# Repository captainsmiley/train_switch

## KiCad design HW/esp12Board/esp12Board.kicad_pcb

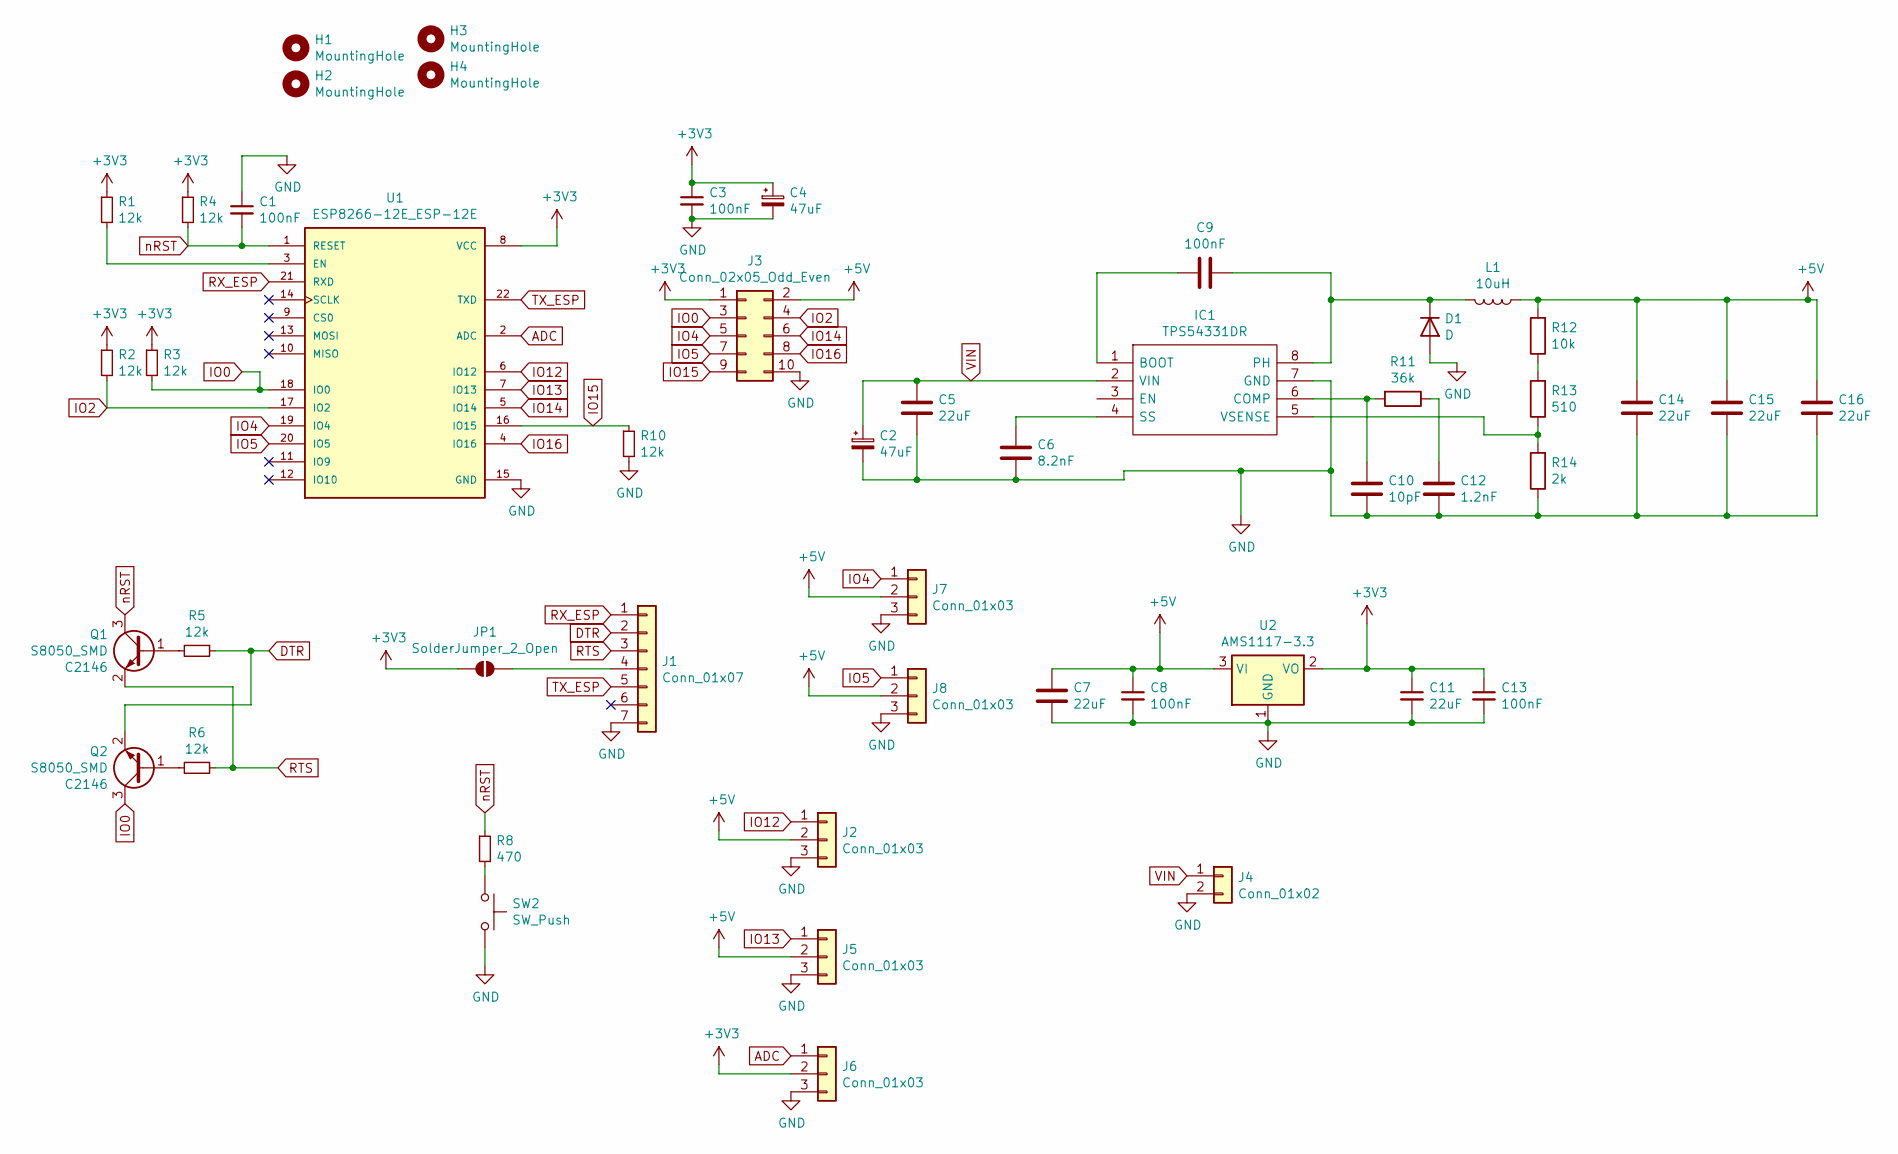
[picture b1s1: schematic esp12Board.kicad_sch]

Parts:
C1, C3, C8, C9, C13: 100nF; C_0805_2012Metric_Pad1.15x1.40mm_HandSolder; LCSC C49678
C2, C4: 47uF; CP_Elec_5x5.7; LCSC C7471868
C5, C7, C11, C14, C15, C16: 22uF; C_0805_2012Metric_Pad1.15x1.40mm_HandSolder; LCSC C45783
C6: 8.2nF; C_0603_1608Metric_Pad1.05x0.95mm_HandSolder; LCSC C1322360
C10: 10pF; C_0603_1608Metric_Pad1.08x0.95mm_HandSolder; LCSC C1634
C12: 1.2nF; C_0603_1608Metric_Pad1.05x0.95mm_HandSolder; LCSC C30615
D1: D; D_SOD-123; LCSC C8598
H1, H2, H3, H4: MountingHole; MountingHole_3.2mm_M3
IC1: TPS54331DR; SOIC127P600X175-8N; Mouser Part Number 595-TPS54331DR
J1: Conn_01x07; PinHeader_1x07_P2.54mm_Vertical
J2, J5, J6, J7, J8: Conn_01x03; PinHeader_1x03_P2.54mm_Vertical; LCSC C6332196
J3: Conn_02x05_Odd_Even; IDC-Header_2x05_P2.54mm_Vertical; LCSC C5372865
J4: Conn_01x02; TerminalBlock_Phoenix_MKDS-1,5-2-5.08_1x02_P5.08mm_Horizont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; LCSC C8465
JP1: SolderJumper_2_Open; SolderJumper-2_P1.3mm_Open_Pad1.0x1.5mm
L1: 10uH; L_Bourns_SRP7028A_7.3x6.6mm; LCSC C132141
Q1, Q2: S8050_SMD; SOT-23; LCSC C2146
R1, R2, R3, R4, R5, R6, R10: 12k; R_0805_2012Metric_Pad1.15x1.40mm_HandSolder; LCSC C17444
R8: 470; R_0805_2012Metric_Pad1.15x1.40mm_HandSolder; LCSC C17710
R11: 36k; R_0805_2012Metric_Pad1.15x1.40mm_HandSolder; LCSC C4360
R12: 10k; R_0805_2012Metric_Pad1.15x1.40mm_HandSolder; LCSC C17414
R13: 510; R_0805_2012Metric_Pad1.15x1.40mm_HandSolder; LCSC C17734
R14: 2k; R_0805_2012Metric_Pad1.15x1.40mm_HandSolder; LCSC C17604
SW2: SW_Push; SW_PUSH_6mm
U1: ESP8266-12E_ESP-12E; ESP-12E; LCSC C82891
U2: AMS1117-3.3; SOT-223-3_TabPin2; LCSC C6186

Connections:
+3V3: C3.1, C4.1, C11.1, C13.1, J3.1, J6.2, JP1.1 (A), R1.1, R2.1, R3.1, R4.1, U1.8 (VCC), U2.2 (VO)
+5V: C7.1, C8.1, C14.1, C15.1, C16.1, J2.2, J3.2, J5.2, J7.2, J8.2, L1.1, R12.2, U2.3 (VI)
ADC: J6.1, U1.2 (ADC)
DTR: J1.2, Q2.2 (E), R5.1
GND: C1.1, C2.2, C3.2, C4.2, C5.2, C6.2, C7.2, C8.2, C10.2, C11.2, C12.2, C13.2, C14.2, C15.2, C16.2, D1.2 (A), IC1.7 (GND), J1.7, J2.3, J3.10, J4.2, J5.3, J6.3, J7.3, J8.3, R10.2, R14.1, SW2.2, U1.15 (GND), U2.1 (GND)
IO0: J3.3, Q2.3 (C), R3.2, U1.18 (IO0)
IO2: J3.4, R2.2, U1.17 (IO2)
IO4: J3.5, J7.1, U1.19 (IO4)
IO5: J3.7, J8.1, U1.20 (IO5)
IO12: J2.1, U1.6 (IO12)
IO13: J5.1, U1.7 (IO13)
IO14: J3.6, U1.5 (IO14)
IO15: J3.9, R10.1, U1.16 (IO15)
IO16: J3.8, U1.4 (IO16)
unnamed: C12.1, R11.1
unnamed: C9.1, D1.1 (K), IC1.8 (PH), L1.2
unnamed: C9.2, IC1.1 (BOOT)
unnamed: C10.1, IC1.6 (COMP), R11.2
unnamed: C6.1, IC1.4 (SS)
unnamed: IC1.5 (VSENSE), R13.1, R14.2
unnamed: J1.4, JP1.2 (B)
unnamed: Q1.1 (B), R5.2
unnamed: Q2.1 (B), R6.2
unnamed: R8.2, SW2.1
unnamed: R12.1, R13.2
unnamed: R1.2, U1.3 (EN)
RTS: J1.3, Q1.2 (E), R6.1
RX_ESP: J1.1, U1.21 (RXD)
TX_ESP: J1.5, U1.22 (TXD)
VIN: C2.1, C5.1, IC1.2 (VIN), J4.1
nRST: C1.2, Q1.3 (C), R4.2, R8.1, U1.1 (RESET)

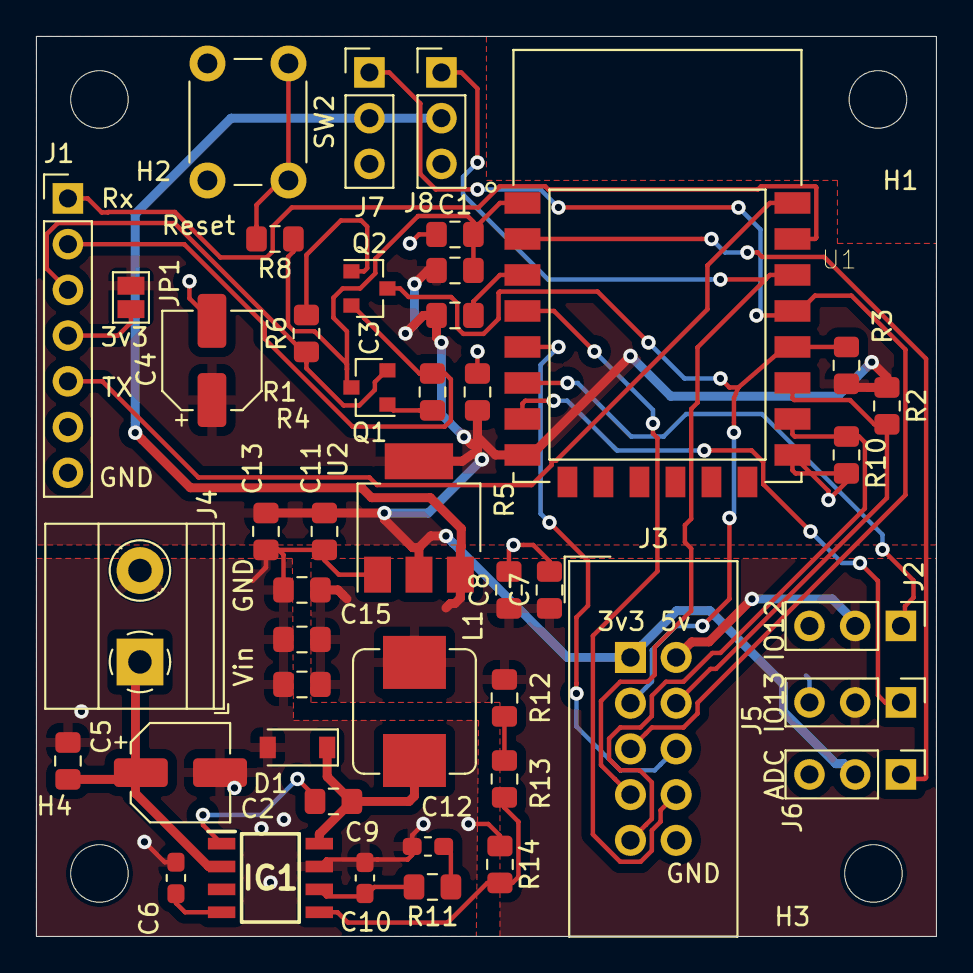
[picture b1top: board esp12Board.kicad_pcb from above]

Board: 2 copper layers, 50.0 x 50.0 mm, 49 parts (0 on the bottom side), 31 nets.

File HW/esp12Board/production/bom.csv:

Designator,Footprint,Quantity,Value,LCSC Part #
"C1, C13, C3, C8, C9",0805,5,100nF,C49678
C10,0603,1,10pF,C1634
"C11, C14, C15, C16, C5, C7",0805,6,22uF,C45783
C12,0603,1,1.2nF,C30615
"C2, C4",CP_Elec_5x5.7,2,47uF, C7471868
C6,0603,1,8.2nF,C1322360
D1,D_SOD-123,1,D,C8598
IC1,SOIC127P600X175-8N,1,TPS54331DR,C9865
J1,PinHeader_1x07_P2.54mm_Vertical,1,Conn_01x07,
"J2, J5, J6, J7, J8",PinHeader_1x03_P2.54mm_Vertical,5,Conn_01x03,C6332196
J3,IDC-Header_2x05_P2.54mm_Vertical,1,Conn_02x05_Odd_Even, C5372865
J4,"TerminalBlock_Phoenix_MKDS-1,5-2-5.08_1x02_P5.08mm_Horizontal",1,Conn_01x02,C8465
L1,L_Bourns_SRP7028A_7.3x6.6mm,1,10uH,C132141
"Q1, Q2",SOT-23,2,S8050_SMD,C2146
"R1, R10, R2, R3, R4, R5, R6",0805,7,12k,C17444
R11,0805,1,36k,C4360
R12,0805,1,10k,C17414
R13,0805,1,510,C17734
R14,0805,1,2k,C17604
R8,0805,1,470,C17710
SW2,SW_PUSH_6mm,1,SW_Push,
U1,ESP-12E,1,ESP8266-12E_ESP-12E,C82891
U2,SOT-223-3_TabPin2,1,AMS1117-3.3,C6186

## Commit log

2017-08-29 :octocat: Added .gitattributes & .gitignore files
2017-11-05 from laptop
2017-11-05 pinnar
2017-11-19 laptop re
2017-11-25 before hack
2017-12-12 holo
2018-01-20 mini hack
2018-01-23 fix merge
2018-02-17 laptop
2021-03-21 HWBoard
2021-05-19 fixes
2021-05-19 Fixed npn orientation added contacts, remove boot sw
2021-05-19 Prep order v3
2024-08-02 update platta HW
2024-08-02 Send msg slower to esp
